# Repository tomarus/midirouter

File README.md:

FPGA/Verilog MIDI Mixer
=======================

See also: 

* https://github.com/tomarus/v-midi
* https://github.com/tomarus/midiseq

This is a "production" version of my FPGA MIDI router.

My v-midi project is more experimental, this one is tuned for my own hardware.

# Disclaimer

Do not use this to learn Verilog or FPGA stuff.

This is my own personal experimental project.

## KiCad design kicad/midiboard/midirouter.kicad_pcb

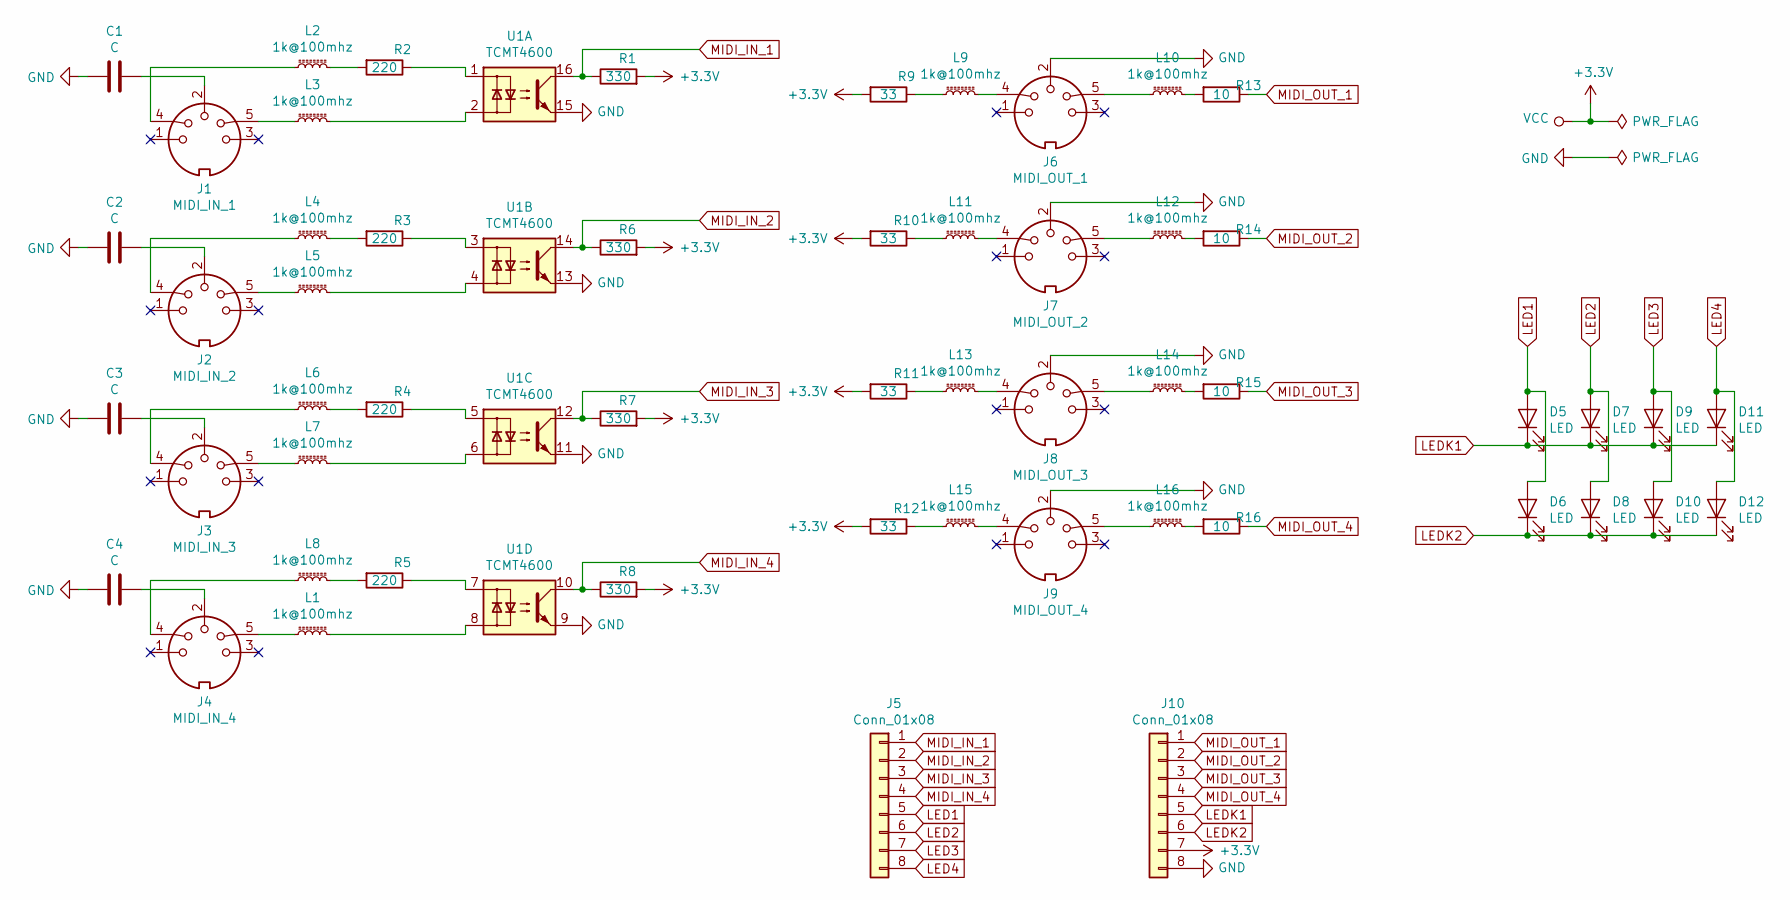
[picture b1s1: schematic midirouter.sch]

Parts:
C1, C2, C3, C4: C; C_0805_2012Metric
D5, D6, D7, D8, D9, D10, D11, D12: LED; LED_D3.0mm
J1: MIDI_IN_1; CUI_SD-50BV
J2: MIDI_IN_2; CUI_SD-50BV
J3: MIDI_IN_3; CUI_SD-50BV
J4: MIDI_IN_4; CUI_SD-50BV
J5, J10: Conn_01x08; PinHeader_1x08_P2.54mm_Vertical
J6: MIDI_OUT_1; CUI_SD-50BV
J7: MIDI_OUT_2; CUI_SD-50BV
J8: MIDI_OUT_3; CUI_SD-50BV
J9: MIDI_OUT_4; CUI_SD-50BV
L1, L2, L3, L4, L5, L6, L7, L8, L9, L10, L11, L12, L13, L14, L15, L16: 1k@100mhz; L_0805_2012Metric_Pad1.15x1.40mm_HandSolder
R1, R6, R7, R8: 330; R_0805_2012Metric
R2, R3, R4, R5: 220; R_0805_2012Metric
R9, R10, R11, R12: 33; R_0805_2012Metric
R13, R14, R15, R16: 10; R_0805_2012Metric
U1: TCMT4600; SOP-16_4.4x10.4mm_P1.27mm

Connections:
+3V3: J10.7, R1.2, R6.2, R7.2, R8.2, R9.2, R10.2, R11.2, R12.2
GND: C1.2, C2.2, C3.2, C4.2, J6.2, J7.2, J8.2, J9.2, J10.8, U1.9, U1.11, U1.13, U1.15
LED1: D5.2 (A), D6.2 (A), J5.5
LED2: D7.2 (A), D8.2 (A), J5.6
LED3: D9.2 (A), D10.2 (A), J5.7
LED4: D11.2 (A), D12.2 (A), J5.8
LEDK1: D5.1 (K), D7.1 (K), D9.1 (K), D11.1 (K), J10.5
LEDK2: D6.1 (K), D8.1 (K), D10.1 (K), D12.1 (K), J10.6
MIDI_IN_1: J5.1, R1.1, U1.16
MIDI_IN_2: J5.2, R6.1, U1.14
MIDI_IN_3: J5.3, R7.1, U1.12
MIDI_IN_4: J5.4, R8.1, U1.10
MIDI_OUT_1: J10.1, R13.1
MIDI_OUT_2: J10.2, R14.1
MIDI_OUT_3: J10.3, R15.1
MIDI_OUT_4: J10.4, R16.1
unnamed: C1.1, J1.2
unnamed: C2.1, J2.2
unnamed: C3.1, J3.2
unnamed: C4.1, J4.2
unnamed: J1.4, L2.1
unnamed: J1.5, L3.1
unnamed: J2.4, L4.1
unnamed: J2.5, L5.1
unnamed: J3.4, L6.1
unnamed: J3.5, L7.1
unnamed: J4.4, L8.1
unnamed: J4.5, L1.1
unnamed: J6.4, L9.2
unnamed: J6.5, L10.1
unnamed: J7.4, L11.2
unnamed: J7.5, L12.1
unnamed: J8.4, L13.2
unnamed: J8.5, L14.1
unnamed: J9.4, L15.2
unnamed: J9.5, L16.1
unnamed: L1.2, U1.8
unnamed: L2.2, R2.2
unnamed: L3.2, U1.2
unnamed: L4.2, R3.2
unnamed: L5.2, U1.4
unnamed: L6.2, R4.2
unnamed: L7.2, U1.6
unnamed: L8.2, R5.2
unnamed: L9.1, R9.1
unnamed: L10.2, R13.2
unnamed: L11.1, R10.1
unnamed: L12.2, R14.2
unnamed: L13.1, R11.1
unnamed: L14.2, R15.2
unnamed: L15.1, R12.1
unnamed: L16.2, R16.2
unnamed: R2.1, U1.1
unnamed: R3.1, U1.3
unnamed: R4.1, U1.5
unnamed: R5.1, U1.7

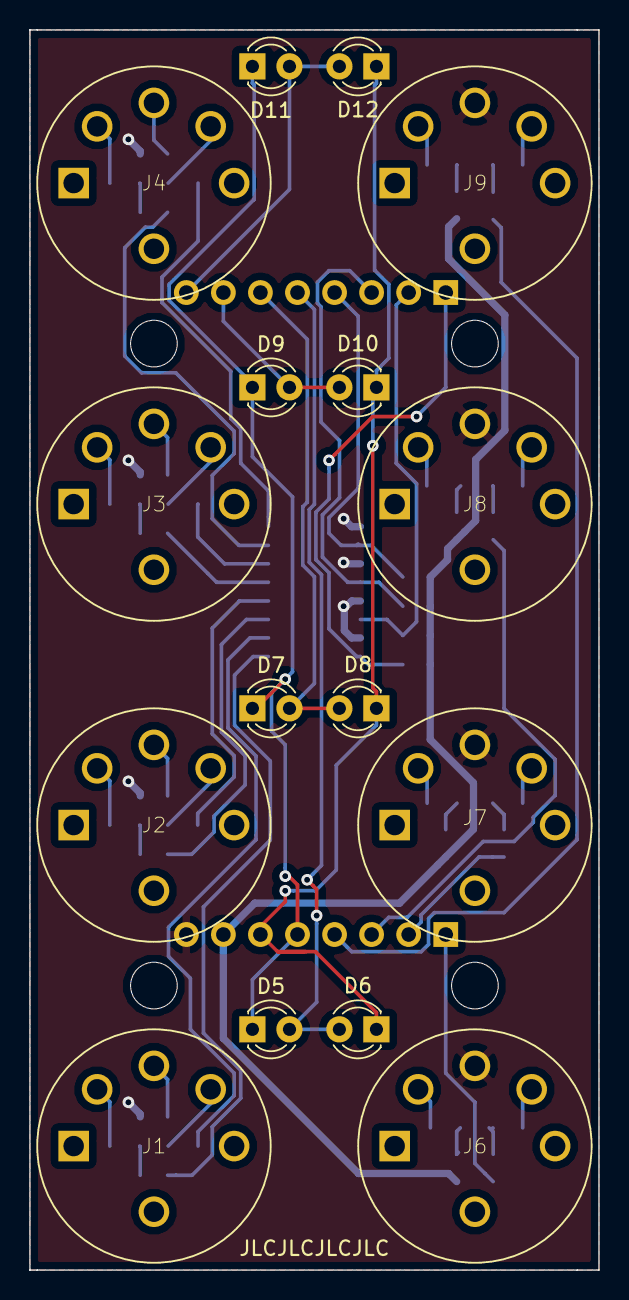
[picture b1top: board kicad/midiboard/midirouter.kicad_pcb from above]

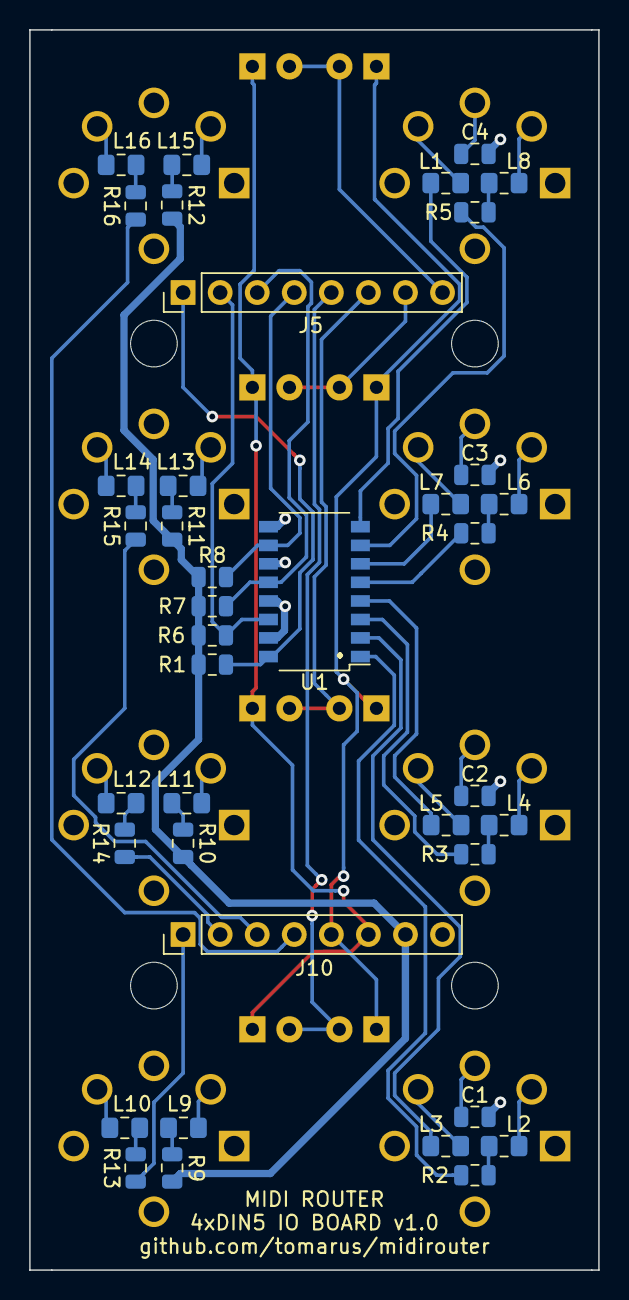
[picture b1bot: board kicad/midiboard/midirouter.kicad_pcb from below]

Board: 2 copper layers, 39.0 x 85.0 mm, 55 parts (39 on the bottom side), 56 nets.

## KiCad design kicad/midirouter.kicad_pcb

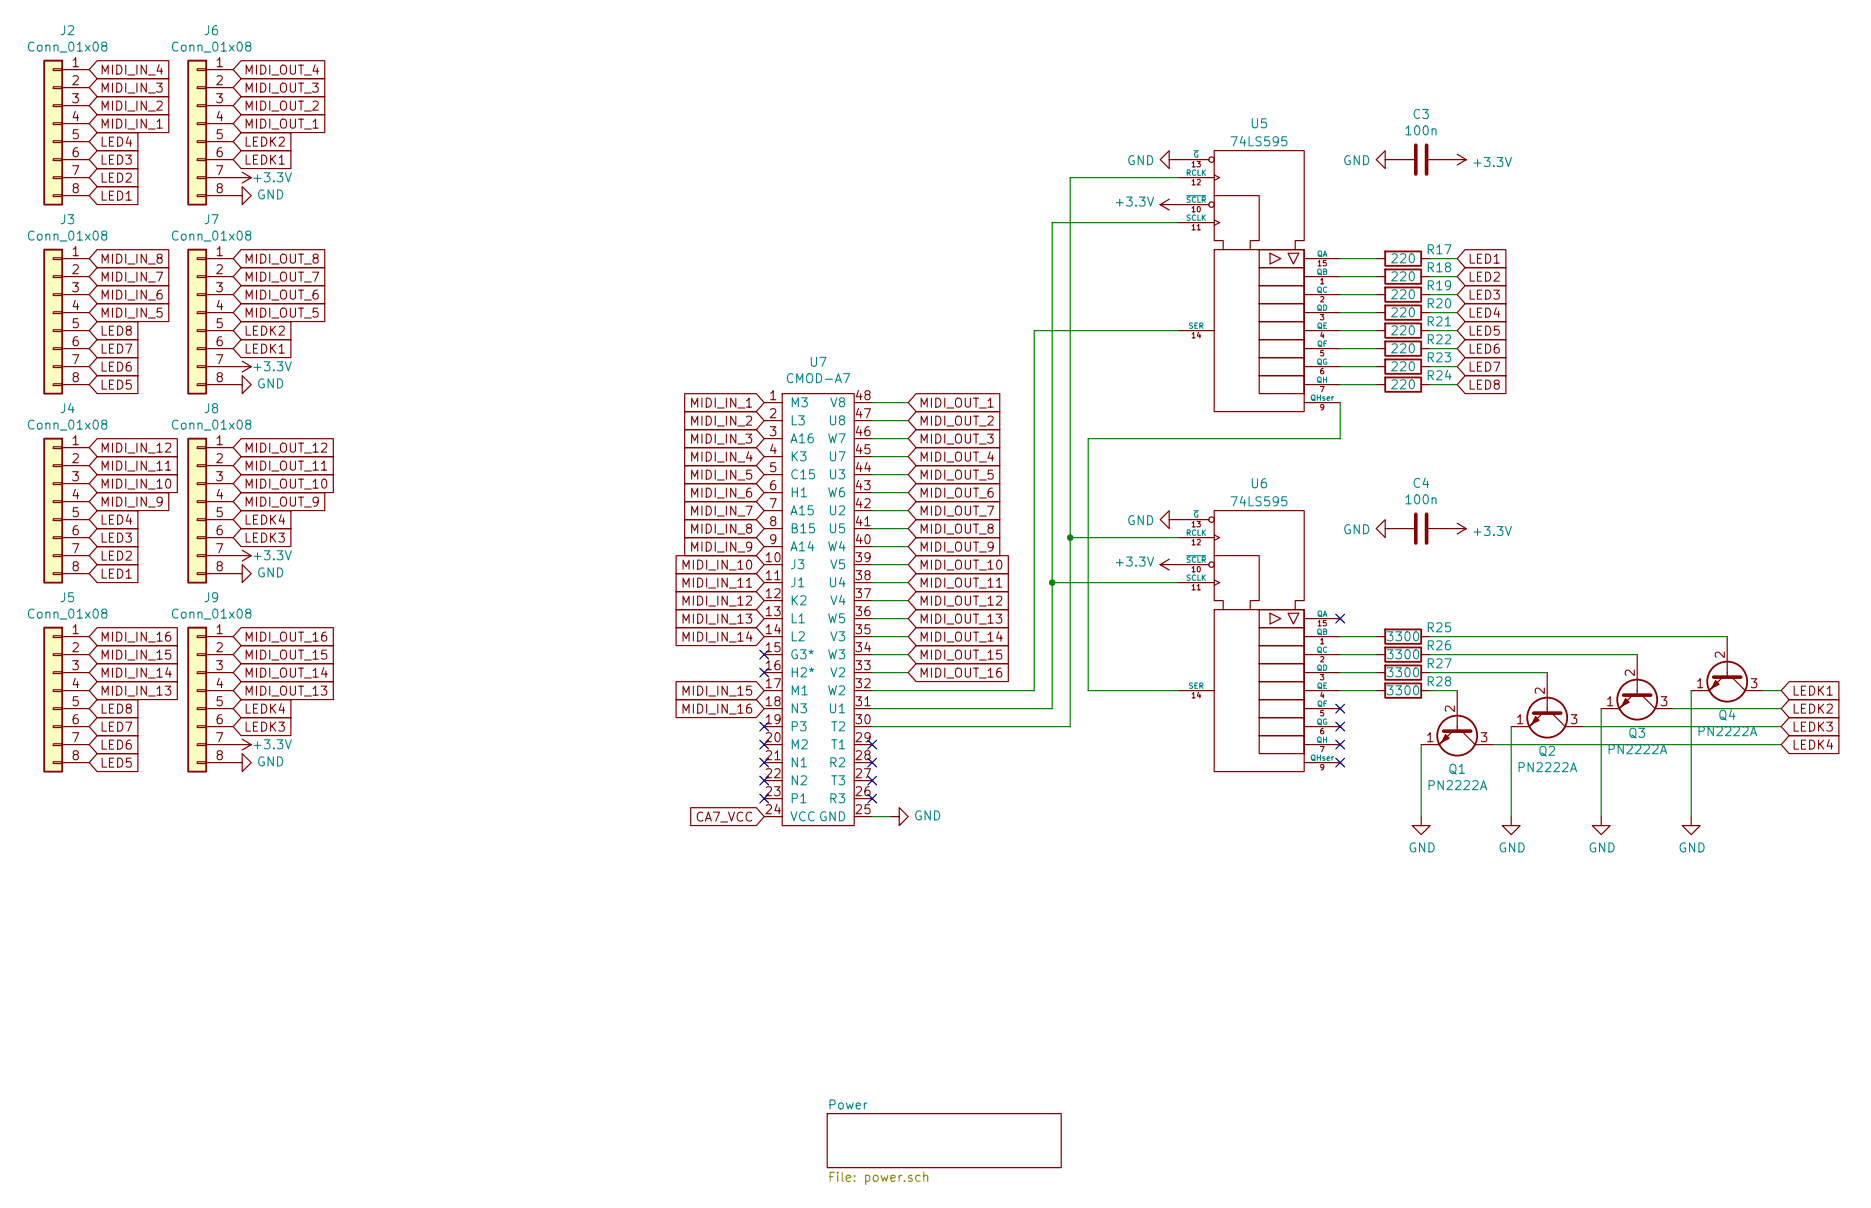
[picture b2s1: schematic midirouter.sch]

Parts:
C3, C4: 100n; C_0805_2012Metric
J2, J3, J4, J5, J6, J7, J8, J9: Conn_01x08; PinSocket_1x08_P2.54mm_Vertical
Q1, Q2, Q3, Q4: PN2222A; MMBT2222A-SOT23
R17, R18, R19, R20, R21, R22, R23, R24: 220; R_0805_2012Metric_Pad1.15x1.40mm_HandSolder
R25, R26, R27, R28: 3300; R_0805_2012Metric_Pad1.15x1.40mm_HandSolder
U5, U6: 74LS595; SOP-16_4.4x10.4mm_P1.27mm
U7: CMOD-A7; CMOD-A7-DIP-48_W15.24mm

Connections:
+3V3: C3.1, C4.1, J6.7, J7.7, J8.7, J9.7, U5.10 (~SCLR), U5.16 (VCC), U6.10 (~SCLR), U6.16 (VCC); also elsewhere on the board
CA7_VCC: U7.24 (VCC); also elsewhere on the board
GND: C3.2, C4.2, J6.8, J7.8, J8.8, J9.8, Q1.1 (E), Q2.1 (E), Q3.1 (E), Q4.1 (E), U5.8 (GND), U5.13 (~G), U6.8 (GND), U6.13 (~G), U7.25 (GND); also elsewhere on the board
LED1: J2.8, J4.8, R17.1
LED2: J2.7, J4.7, R18.1
LED3: J2.6, J4.6, R19.1
LED4: J2.5, J4.5, R20.1
LED5: J3.8, J5.8, R21.1
LED6: J3.7, J5.7, R22.1
LED7: J3.6, J5.6, R23.1
LED8: J3.5, J5.5, R24.1
LEDK1: J6.6, J7.6, Q4.3 (C)
LEDK2: J6.5, J7.5, Q3.3 (C)
LEDK3: J8.6, J9.6, Q2.3 (C)
LEDK4: J8.5, J9.5, Q1.3 (C)
MIDI_IN_1: J2.4, U7.1 (M3)
MIDI_IN_2: J2.3, U7.2 (L3)
MIDI_IN_3: J2.2, U7.3 (A16)
MIDI_IN_4: J2.1, U7.4 (K3)
MIDI_IN_5: J3.4, U7.5 (C15)
MIDI_IN_6: J3.3, U7.6 (H1)
MIDI_IN_7: J3.2, U7.7 (A15)
MIDI_IN_8: J3.1, U7.8 (B15)
MIDI_IN_9: J4.4, U7.9 (A14)
MIDI_IN_10: J4.3, U7.10 (J3)
MIDI_IN_11: J4.2, U7.11 (J1)
MIDI_IN_12: J4.1, U7.12 (K2)
MIDI_IN_13: J5.4, U7.13 (L1)
MIDI_IN_14: J5.3, U7.14 (L2)
MIDI_IN_15: J5.2, U7.17 (M1)
MIDI_IN_16: J5.1, U7.18 (N3)
MIDI_OUT_1: J6.4, U7.48 (V8)
MIDI_OUT_2: J6.3, U7.47 (U8)
MIDI_OUT_3: J6.2, U7.46 (W7)
MIDI_OUT_4: J6.1, U7.45 (U7)
MIDI_OUT_5: J7.4, U7.44 (U3)
MIDI_OUT_6: J7.3, U7.43 (W6)
MIDI_OUT_7: J7.2, U7.42 (U2)
MIDI_OUT_8: J7.1, U7.41 (U5)
MIDI_OUT_9: J8.4, U7.40 (W4)
MIDI_OUT_10: J8.3, U7.39 (V5)
MIDI_OUT_11: J8.2, U7.38 (U4)
MIDI_OUT_12: J8.1, U7.37 (V4)
MIDI_OUT_13: J9.4, U7.36 (W5)
MIDI_OUT_14: J9.3, U7.35 (V3)
MIDI_OUT_15: J9.2, U7.34 (W3)
MIDI_OUT_16: J9.1, U7.33 (V2)
unnamed: Q1.2 (B), R28.1
unnamed: Q2.2 (B), R27.1
unnamed: Q3.2 (B), R26.1
unnamed: Q4.2 (B), R25.1
unnamed: R17.2, U5.15 (QA)
unnamed: R18.2, U5.1 (QB)
unnamed: R19.2, U5.2 (QC)
unnamed: R20.2, U5.3 (QD)
unnamed: R21.2, U5.4 (QE)
unnamed: R22.2, U5.5 (QF)
unnamed: R23.2, U5.6 (QG)
unnamed: R24.2, U5.7 (QH)
unnamed: R25.2, U6.1 (QB)
unnamed: R26.2, U6.2 (QC)
unnamed: R27.2, U6.3 (QD)
unnamed: R28.2, U6.4 (QE)
unnamed: U5.9 (QHser), U6.14 (SER)
unnamed: U5.11 (SCLK), U6.11 (SCLK), U7.31 (U1)
unnamed: U5.12 (RCLK), U6.12 (RCLK), U7.30 (T2)
unnamed: U5.14 (SER), U7.32 (W2)

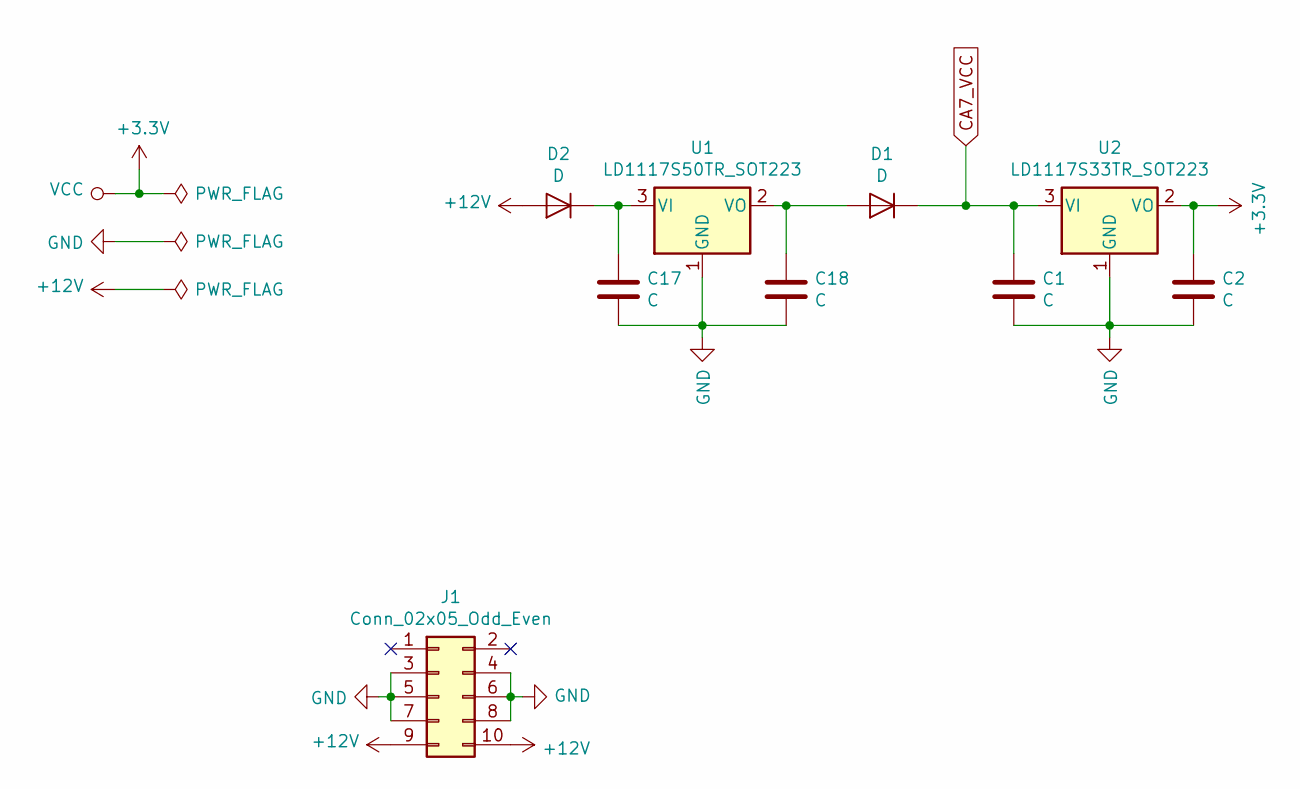
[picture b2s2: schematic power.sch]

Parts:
C1, C2, C17, C18: C; CP_Elec_5x3.9
D1, D2: D; D_0805_2012Metric_Pad1.15x1.40mm_HandSolder
J1: Conn_02x05_Odd_Even; IDC-Header_2x05_P2.54mm_Vertical
U1: LD1117S50TR_SOT223; SOT-223-3_TabPin2
U2: LD1117S33TR_SOT223; SOT-223-3_TabPin2

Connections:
+3V3: C2.1, U2.2 (VO); also elsewhere on the board
+12V: D2.2 (A), J1.9, J1.10
CA7_VCC: C1.1, D1.1 (K), U2.3 (VI); also elsewhere on the board
GND: C1.2, C2.2, C17.2, C18.2, J1.3, J1.4, J1.5, J1.6, J1.7, J1.8, U1.1 (GND), U2.1 (GND); also elsewhere on the board
unnamed: C17.1, D2.1 (K), U1.3 (VI)
unnamed: C18.1, D1.2 (A), U1.2 (VO)

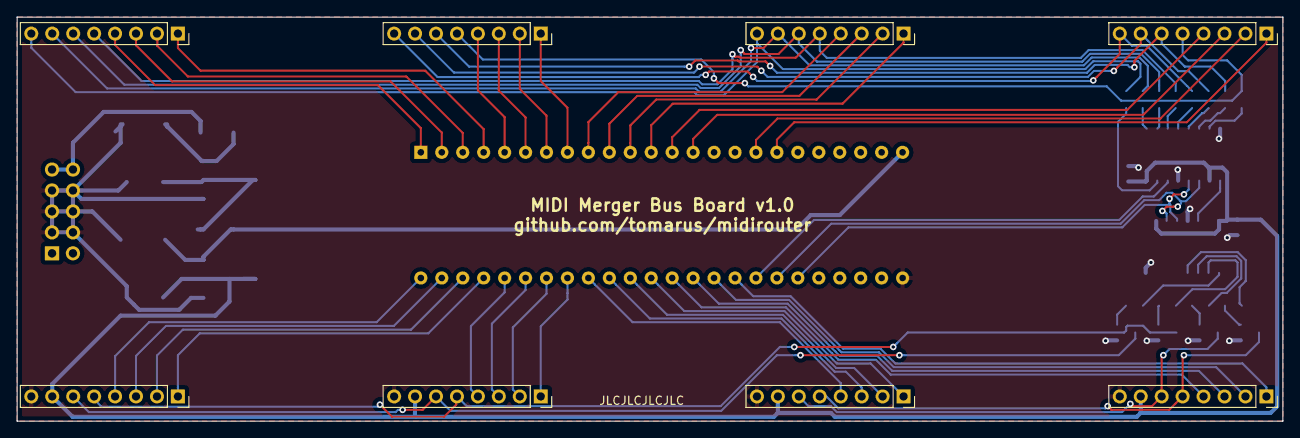
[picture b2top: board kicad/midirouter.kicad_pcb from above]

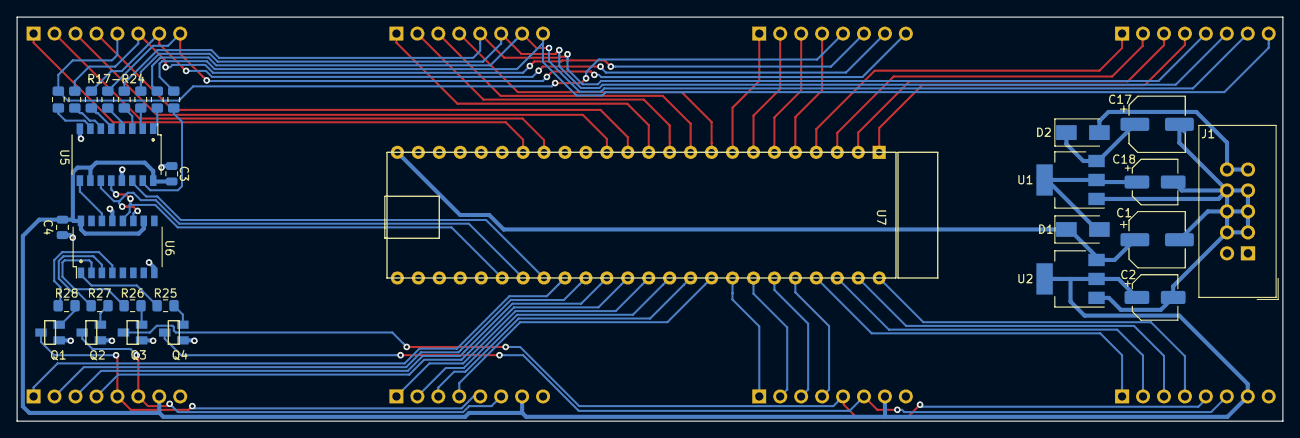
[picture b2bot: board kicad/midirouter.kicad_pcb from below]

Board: 2 copper layers, 153.5 x 49.0 mm, 38 parts (30 on the bottom side), 70 nets.

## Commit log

2018-07-24 Initial commit.
2018-07-25 Fix some small stuff.
2018-07-25 Reverse rows and collums for better power distribution.
2018-07-25 Remove commented out line.
2018-07-25 Improve some comments and defaults.
2018-07-31 Change activity leds duration and config to 16 ports.
2018-07-31 Add License
2018-09-02 Small updates to activity leds, avoid looping/routing on current port.
2018-09-02 Cleanup a bit.
2018-09-08 Small cleanups.
2018-10-02 Final fix leds
2018-10-02 Move around some stuff.
2018-10-02 Update project settings.
2018-10-02 Update project paths.
2018-10-03 Add screensaver.
2018-10-03 Change CLOCK to CLKS_PER_BIT.
2018-10-03 Update project files.
2018-10-03 Add (eagle) schematics and boards.
2018-10-03 Add Verilator code and some misc updates.
2018-10-03 Reformat and linter fixes.
2018-10-03 Keep our trace save file.
2018-10-07 Implement merging, more buffering, lots of other small stuff.
2018-10-07 Shave off some LUT usage using a global activity-led delay.
2018-10-08 Fix some bugs, better naming.
2018-10-08 Move around / cleanup some stuff.
2018-10-12 Make the merger work and merge everything by default.
2018-10-12 Add Go utilities midimonitor and configurator.
2018-10-14 Fix clock byte merging.
2018-10-14 Fix some warnings, fix some tabs vs spaces.
2018-10-14 More spaces vs tabs fixes.
2018-10-14 Some more identation & spaces vs tabs fixes.
2018-10-16 Fix more tabs vs spaces.
2018-10-21 Add procedural midi song generator and player.
2018-10-21 Add some startup error checking.
2018-10-21 Simplify a bit.
2018-10-21 Add piano song.
2018-10-27 Shorten led activity flicker, Fix linter warnings, Disable port 7 because its broken.
2018-10-27 Add random gates / drum sequencer.
2018-10-28 Remove test stuff, Rename onoff to gate, Fiddle with test song 3.
2018-10-28 Add soundcloud links to demo patterns.
2019-12-23 Small updates & fixes to the Go tools.
2019-12-23 Add some old pdf schematics.
2019-12-23 Try out large memory and multi-port fifos. Doesnt work atm.
2019-12-23 Add first kicad tryouts.
2019-12-23 Update gitignore.
2019-12-28 First working version using Microblaze design.
2019-12-28 Ignore clock/activesensing for activity, reduce activity length + misc fixes & updates.
2019-12-28 Remove metadata.
2019-12-29 Fix clock merging, smallish other updates.
2019-12-30 Fix clock detection.
2020-01-01 Work on schematics and pcbs.
2020-01-02 Increase mem from 32k to 64k, Add xspi flash config management.
2020-01-02 Add sysex processing, info + dump command.
2020-01-02 Fix/Update minor stuff.
2020-01-03 Work on pcbs a bit.
2020-01-04 More work on pcbs and frontpanel.
2020-01-04 Switch to TCMT4600 and increase size of ferrites.
2020-01-07 Work on base pcb/schematics + frontpanel.
2020-01-14 Updates to frontpanels, schematics and pcbs.
2020-01-15 Move all kicad stuff to kicad/ dir.
2020-01-15 Remove old Eagle files.
2020-01-15 Fix for last commit.
2020-01-15 Fix for last commit, and the one before that.
2020-01-15 Silkscreen and text updates.
2020-01-26 Some minor silkscreen updates.
2020-04-26 Revision A PCBs.
2020-05-30 New design, update LED driver for 595.
2020-05-30 Add LED/Port identification command.
2020-06-02 Swap Input and Output for activity LEDs.
